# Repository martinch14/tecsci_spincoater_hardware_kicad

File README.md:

# tecsci_spincoater_hardware_kicad

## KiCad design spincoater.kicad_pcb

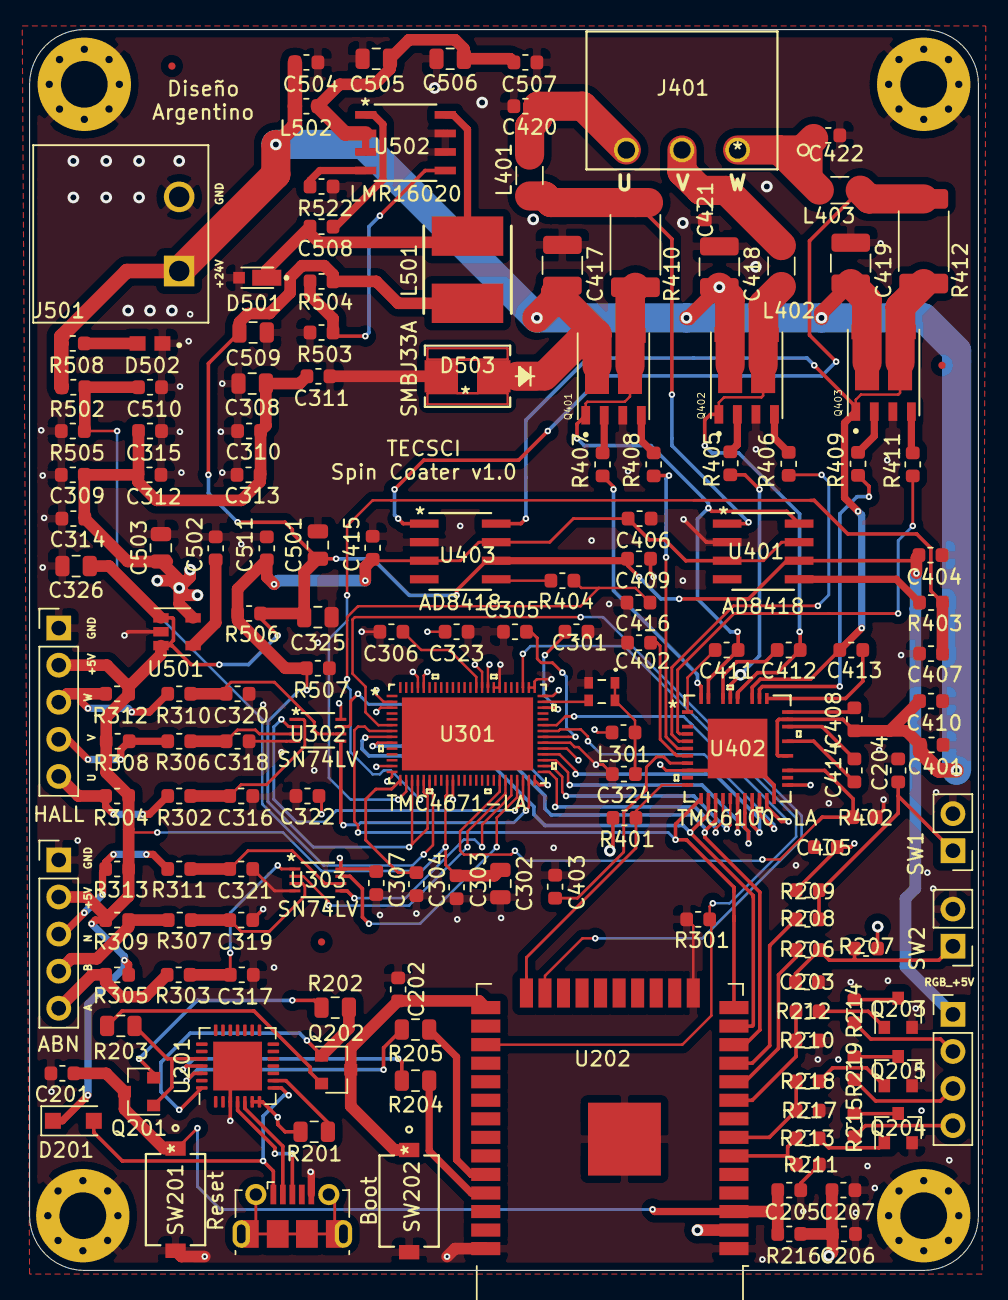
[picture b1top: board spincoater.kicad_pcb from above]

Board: 4 copper layers, 65.0 x 85.0 mm, 164 parts (0 on the bottom side), 112 nets.

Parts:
C201, C202, C205, C207: 0.1uF/50V/0603; C_0603_1608Metric
C203, C204, C301, C303, C304, C305, C306, C307, C310, C311, C312, C313, C314, C315, C322, C323, C404, C405, C406, C408, C409, C410, C415, C504, C507, C508, C510, C511: 100nF/50V/0603; C_0603_1608Metric
C206: 22uF/10V/0603; C_0603_1608Metric
C302, C308: 4.7uF/16V/0805; C_0805_2012Metric
C309, C411, C412, C413: 470nF/50V/0603; C_0603_1608Metric
C316, C317, C318, C319, C320, C321, C420, C421, C422: 1nF/100V/0603; C_0603_1608Metric
C324: 100nF/50V 0603; C_0603_1608Metric
C325, C326: 1uF/50V/0805; C_0805_2012Metric
C401: 100nF/50v/0603; C_0603_1608Metric
C402, C403: 2.2uF/16V/0603; C_0603_1608Metric
C407, C416: 2.2nF/50V/0603; C_0603_1608Metric
C414: 22nF/100V/0603; C_0603_1608Metric
C417, C418, C419: 10uF/50V/1210; C_1210_3225Metric
C501, C503, C509: 10uF/16V/0805; C_0805_2012Metric
C502: 10nF/16V/0603; C_0603_1608Metric
C505, C506: 2.2uF/50V/0805; C_0805_2012Metric
D201: PMEG3020EH; D_SOD-123F
D501: V2PM10HM3; DIODE_MSS1P4-M3
D502: LTST-C191TBKT-5A
D503: SMBJ33A; SMBJ33A-13-F
FID101, FID102, FID103: Fiducial; Fiducial_0.5mm_Mask1mm
H101, H102, H103, H104: MountingHole_Pad; MountingHole_3.2mm_M3_Pad_Via
J201: USB_B_Micro; USB_Micro-B_Molex-105017-0001
J202, J203: Conn_01x02; PinHeader_1x02_P2.54mm_Vertical
J204: Conn_01x04; PinHeader_1x04_P2.54mm_Vertical
J301, J302: Conn_01x05; PinHeader_1x05_P2.54mm_Vertical
J401: 1803280
J501: 1757242; PHOENIX_1757242
L301, L502: 600R/1A/0603; L_0603_1608Metric
L401, L402, L403: 50R/12A/1206; L_1206_3216Metric
L501: 15uH/2.5A/VLS6045; INDPM6060X450N
Q201, Q202: S8050; SOT-23
Q203, Q204, Q205: 2N7002; SOT-23
Q401, Q402, Q403: SI7288DP-T1-GE3; TRANS_SI7288DP-T1-GE3
R201: 4.7K/1%/0805; R_0805_2012Metric
R202, R203: 10K/1%/0805; R_0805_2012Metric
R204, R205: 1K/1%/0805; R_0805_2012Metric
R206, R208, R403, R506, R507: 1K/1%/0603; R_0603_1608Metric
R207, R209, R212, R213, R216, R218, R301, R401, R402, R505, R508: 10K/1%/0603; R_0603_1608Metric
R210, R211, R217: 330K/1%/0603; R_0603_1608Metric
R214, R215, R219: 680/1%/0603; R_0603_1608Metric
R302, R303, R304, R305, R306, R307, R308, R309, R310, R311, R312, R313: 4K7/1%/0603; R_0603_1608Metric
R404: 1k/1%/0603; R_0603_1608Metric
R405, R406, R407, R408, R409, R411: 10R/1%/0603; R_0603_1608Metric
R410, R412: 0R005/1%/3W/2512; R_2512_6332Metric
R502: 220K/1%/0603; R_0603_1608Metric
R503: 47K/1%/0603; R_0603_1608Metric
R504: 270K/1%/0603; R_0603_1608Metric
R522: 33K/1%/0603; R_0603_1608Metric
SW201: Reset; KSR223GLFG
SW202: Boot; KSR223GLFG
U201: CP2102N-A01-GQFN28; QFN-28-1EP_5x5mm_P0.5mm_EP3.35x3.35mm
U202: ESP32-WROOM-32D; ESP32-WROOM-32
U301: TMC4671-LA
U302, U303: SN74LV; SN74LVC3G17DCURE4
U401, U403: AD8418; AD8418WBRZ-RL
U402: TMC6100-LA
U501: LP2985-3.3; SOT-23-5
U502: LMR16020; LMR16020PDDAR
Y301: MC2016K25.0000C16ESH; MC2016K250000C16ESH

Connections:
+2.5V_REF: C406.1, C415.1, C511.1, R506.2, R507.1, U301.17, U301.19, U401.3, U401.7, U403.3, U403.7
+3V3: C206.1, C207.1, C307.1, C308.1, C309.1, C310.1, C311.1, C312.1, C313.1, C314.1, C315.1, C322.1, C323.2, C405.1, C503.1, L301.1, R201.1, R207.2, R209.2, R216.2, R401.1, U201.6, U201.7, U202.2, U301.2, U301.13, U301.43, U301.52, U301.61, U301.72, U302.8, U303.8, U402.16, U402.22, U501.5
+5V: C302.1, C303.1, C325.1, C326.1, C404.1, C409.1, C501.1, C509.1, D201.1, J204.1, J301.2, J302.2, L501.2, R304.2, R305.1, R308.1, R309.1, R312.2, R313.1, R504.1, R506.1, U301.23, U401.6, U403.6, U501.1, U501.3
+24V: C401.1, C408.1, C410.1, C417.1, C418.1, C419.1, C504.1, D503.1, J501.1, L502.1, Q401.7, Q401.8, Q401.9, Q402.7, Q402.8, Q402.9, Q403.7, Q403.8, Q403.9, R502.1, R508.1, U402.25, U402.28
/driverMotor/HSU: R407.2, U402.37
/driverMotor/HSV: R405.2, U402.34
/driverMotor/HSW: R409.2, U402.31
/driverMotor/LSU: R408.2, U402.5
/driverMotor/LSV: R406.2, U402.4
/driverMotor/LSW: R411.2, U402.3
/driverMotor/U: L401.1, R410.1, U401.1
/driverMotor/U_SENSE: C411.1, Q401.1, Q401.5, Q401.6, Q401.10, R410.2, U401.8, U402.36
/driverMotor/V: C412.1, L402.1, Q402.1, Q402.5, Q402.6, Q402.10, U402.33
/driverMotor/W: L403.1, R412.1, U403.1
/driverMotor/W_SENSE: C413.1, Q403.1, Q403.5, Q403.6, Q403.10, R412.2, U402.32, U403.8
/microcontroladorEsp/D+: J201.3, U201.4
/microcontroladorEsp/D-: J201.2, U201.5
/microcontroladorEsp/DTR: Q202.1, R202.2, U201.28
/microcontroladorEsp/EN: C201.1, C205.1, Q201.3, R216.1, SW201.1, U202.3
/microcontroladorEsp/IO0: C202.1, Q202.3, SW202.1, U202.25
/microcontroladorEsp/LED1: R210.1, R212.1, U202.9
/microcontroladorEsp/LED2: R211.1, R213.1, U202.6
/microcontroladorEsp/LED3: R217.1, R218.1, U202.7
/microcontroladorEsp/RTS: Q201.1, R203.2, U201.24
/microcontroladorEsp/RX: R205.1, U202.34
/microcontroladorEsp/SW1: R206.1, U202.10
/microcontroladorEsp/SW2: R208.1, U202.11
/microcontroladorEsp/TX: R204.1, U202.35
/microcontroladorEsp/VBUS: D201.2, J201.1, U201.8
ADC_+24: C510.1, R502.2, R505.1, U301.20
CS_4671: U202.23, U301.6
CS_6100: R401.2, U202.24, U402.10
CUR_U: C407.1, R403.1, U301.16
CUR_W: C416.1, R404.1, U301.18
EN_4671: R301.1, U202.27, U301.55
EN_6100: R402.2, U301.32, U402.24
GND: C201.2, C202.2, C203.2, C204.2, C205.2, C206.2, C207.2, C301.2, C302.2, C303.2, C304.2, C305.2, C306.2, C307.2, C308.2, C309.2, C310.2, C311.2, C312.2, C313.2, C314.2, C315.2, C316.2, C317.2, C318.2, C319.2, C320.2, C321.2, C322.2, C323.1, C324.2, C325.2, C326.2, C401.2, C402.2, C403.2, C404.2, C405.2, C406.2, C407.2, C409.2, C410.2, C415.2, C416.2, C417.2, C418.2, C419.2, C420.2, C421.2, C422.2, C501.2, C502.2, C503.2, C504.2, C505.2, C506.2, C507.2, C509.2, C510.2, C511.2, D501.2, D502.1, D503.2, H101.1, H102.1, H103.1, H104.1, J201.5, J202.2, J203.2, J301.1, J302.1, J501.2, Q203.2, Q204.2, Q205.2, Q401.3, Q402.3, Q403.3, R210.2, R211.2, R217.2, R301.2, R402.1, R503.2, R505.2, R507.2, R522.2, SW201.2, SW202.2, U201.3, U201.29, U202.1, U202.15, U202.38, U202.39, U301.3, U301.14, U301.24, U301.44, U301.53, U301.54, U301.59, U301.60, U301.62, U301.73, U302.4, U303.4, U401.2, U402.8, U402.21, U402.38, U403.2, U501.2, U502.6, U502.7, Y301.2
unnamed: C203.1, J202.1, R206.2, R207.1
unnamed: C204.1, J203.1, R208.2, R209.1
unnamed: C301.1, U301.50
unnamed: C304.1, U301.15
unnamed: C305.1, U301.45
unnamed: C306.1, U301.63
unnamed: C316.1, R302.2, U302.1
unnamed: C317.1, R303.1, U303.1
unnamed: C318.1, R306.1, U302.3
unnamed: C319.1, R307.1, U303.3
unnamed: C320.1, R310.2, U302.6
unnamed: C321.1, R311.1, U303.6
unnamed: C324.1, L301.2, Y301.1, Y301.4
unnamed: C402.1, U402.6
unnamed: C403.1, U402.7
unnamed: C408.2, U402.29
unnamed: C411.2, U402.1
unnamed: C412.2, U402.35
unnamed: C413.2, U402.30
unnamed: C414.1, U402.26
unnamed: C414.2, U402.27
unnamed: C420.1, J401.3, L401.2
unnamed: C421.1, J401.2, L402.2
unnamed: C422.1, J401.1, L403.2
unnamed: C502.1, U501.4
unnamed: C505.1, C506.1, C507.1, L502.2, U502.2, U502.3
unnamed: C508.1, D501.1, L501.1, U502.8
unnamed: C508.2, U502.1
unnamed: D502.2, R508.2
unnamed: J204.2, R214.1
unnamed: J204.3, R219.1
unnamed: J204.4, R215.1
unnamed: J301.3, R310.1, R312.1
unnamed: J301.4, R306.2, R308.2
unnamed: J301.5, R302.1, R304.1
unnamed: J302.3, R311.2, R313.2
unnamed: J302.4, R307.2, R309.2
unnamed: J302.5, R303.2, R305.2
unnamed: Q201.2, R202.1
unnamed: Q202.2, R203.1
unnamed: Q203.1, R212.2
unnamed: Q203.3, R214.2
unnamed: Q204.1, R213.2
unnamed: Q204.3, R215.2
unnamed: Q205.1, R218.2
unnamed: Q205.3, R219.2
unnamed: Q401.2, R407.1
unnamed: Q401.4, R408.1
unnamed: Q402.2, R405.1
unnamed: Q402.4, R406.1
unnamed: Q403.2, R409.1
unnamed: Q403.4, R411.1
unnamed: R201.2, U201.9
unnamed: R204.2, U201.25
unnamed: R205.2, U201.26
unnamed: R403.2, U401.5
unnamed: R404.2, U403.5
unnamed: R503.1, R504.2, U502.5
unnamed: R522.1, U502.4
unnamed: U301.33, U303.2
unnamed: U301.34, U303.5
unnamed: U301.35, U303.7
unnamed: U301.36, U302.2
unnamed: U301.37, U302.5
unnamed: U301.38, U302.7
unnamed: U301.51, Y301.3
SPI_MISO: U202.12, U301.9, U402.13
SPI_MOSI: U202.13, U301.8, U402.12
SPI_SCK: U202.14, U301.7, U402.11
UH: U301.39, U402.14
UL: U301.40, U402.15
VH: U301.41, U402.17
VL: U301.42, U402.18
WH: U301.46, U402.19
WL: U301.47, U402.20

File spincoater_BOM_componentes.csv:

"Id";"Designator";"Package";"Quantity";"Designation";"Supplier and ref";
1;"J204";"PinHeader_1x04_P2.54mm_Vertical";1;"Conn_01x04";;;
2;"R219,R215,R214";"R_0603_1608Metric";3;"680/1%/0603";;;
3;"R218,R508,R505,R402,R401,R301,R216,R213,R212,R209,R207";"R_0603_1608Metric";11;"10K/1%/0603";;;
4;"R217,R211,R210";"R_0603_1608Metric";3;"330K/1%/0603";;;
5;"Q205,Q204,Q203";"SOT-23";3;"2N7002";;;
6;"C504,C306,C511,C510,C508,C507,C415,C410,C409,C408,C406,C405,C404,C323,C322,C315,C314,C313,C312,C311,C310,C307,C305,C304,C303,C301,C204,C203";"C_0603_1608Metric";28;"100nF/50V/0603";;;
7;"U202";"ESP32-WROOM-32";1;"ESP32-WROOM-32D";;;
8;"D503";"SMBJ33A-13-F";1;"SMBJ33A";;;
9;"Q202,Q201";"SOT-23";2;"S8050";;;
10;"Y301";"MC2016K250000C16ESH";1;"MC2016K25.0000C16ESH";;;
11;"U502";"LMR16020PDDAR";1;"LMR16020";;;
12;"U501";"SOT-23-5";1;"LP2985-3.3";;;
13;"U403,U401";"AD8418WBRZ-RL";2;"AD8418";;;
14;"U402";"TMC6100-LA";1;"TMC6100-LA";;;
15;"U303,U302";"SN74LVC3G17DCURE4";2;"SN74LV";;;
16;"U301";"TMC4671-LA";1;"TMC4671-LA";;;
17;"U201";"QFN-28-1EP_5x5mm_P0.5mm_EP3.35x3.35mm";1;"CP2102N-A01-GQFN28";;;
18;"SW202";"KSR223GLFG";1;"Boot";;;
19;"SW201";"KSR223GLFG";1;"Reset";;;
20;"R522";"R_0603_1608Metric";1;"33K/1%/0603";;;
21;"R507,R506,R403,R208,R206";"R_0603_1608Metric";5;"1K/1%/0603";;;
22;"R504";"R_0603_1608Metric";1;"270K/1%/0603";;;
23;"R503";"R_0603_1608Metric";1;"47K/1%/0603";;;
24;"R502";"R_0603_1608Metric";1;"220K/1%/0603";;;
25;"R412,R410";"R_2512_6332Metric";2;"0R005/1%/3W/2512";;;
26;"R411,R409,R408,R407,R406,R405";"R_0603_1608Metric";6;"10R/1%/0603";;;
27;"R404";"R_0603_1608Metric";1;"1k/1%/0603";;;
28;"R313,R312,R311,R310,R309,R308,R307,R306,R305,R304,R303,R302";"R_0603_1608Metric";12;"4K7/1%/0603";;;
29;"R205,R204";"R_0805_2012Metric";2;"1K/1%/0805";;;
30;"R203,R202";"R_0805_2012Metric";2;"10K/1%/0805";;;
31;"R201";"R_0805_2012Metric";1;"4.7K/1%/0805";;;
32;"Q403,Q402,Q401";"TRANS_SI7288DP-T1-GE3";3;"SI7288DP-T1-GE3";;;
33;"L502,L301";"L_0603_1608Metric";2;"600R/1A/0603";;;
34;"L501";"INDPM6060X450N";1;"15uH/2.5A/VLS6045";;;
35;"L403,L402,L401";"L_1206_3216Metric";3;"50R/12A/1206";;;
36;"J501";"PHOENIX_1757242";1;"1757242";;;
37;"J401";"1803280";1;"1803280";;;
38;"J302,J301";"PinHeader_1x05_P2.54mm_Vertical";2;"Conn_01x05";;;
39;"J203,J202";"PinHeader_1x02_P2.54mm_Vertical";2;"Conn_01x02";;;
40;"J201";"USB_Micro-B_Molex-105017-0001";1;"USB_B_Micro";;;
41;"H104,H103,H102,H101";"MountingHole_3.2mm_M3_Pad_Via";4;"MountingHole_Pad";;;
42;"FID103,FID102,FID101";"Fiducial_0.5mm_Mask1mm";3;"Fiducial";;;
43;"D502";"LTST-C191TBKT-5A";1;"LTST-C191TBKT-5A";;;
44;"D501";"DIODE_MSS1P4-M3";1;"V2PM10HM3";;;
45;"D201";"D_SOD-123F";1;"PMEG3020EH";;;
46;"C509,C503,C501";"C_0805_2012Metric";3;"10uF/16V/0805";;;
47;"C506,C505";"C_0805_2012Metric";2;"2.2uF/50V/0805";;;
48;"C502";"C_0603_1608Metric";1;"10nF/16V/0603";;;
49;"C422,C421,C420,C321,C320,C319,C318,C317,C316";"C_0603_1608Metric";9;"1nF/100V/0603";;;
50;"C419,C418,C417";"C_1210_3225Metric";3;"10uF/50V/1210";;;
51;"C416,C407";"C_0603_1608Metric";2;"2.2nF/50V/0603";;;
52;"C414";"C_0603_1608Metric";1;"22nF/100V/0603";;;
53;"C413,C412,C411,C309";"C_0603_1608Metric";4;"470nF/50V/0603";;;
54;"C403,C402";"C_0603_1608Metric";2;"2.2uF/16V/0603";;;
55;"C401";"C_0603_1608Metric";1;"100nF/50v/0603";;;
56;"C326,C325";"C_0805_2012Metric";2;"1uF/50V/0805";;;
57;"C324";"C_0603_1608Metric";1;"100nF/50V 0603";;;
58;"C308,C302";"C_0805_2012Metric";2;"4.7uF/16V/0805";;;
59;"C207,C205,C202,C201";"C_0603_1608Metric";4;"0.1uF/50V/0603";;;
60;"C206";"C_0603_1608Metric";1;"22uF/10V/0603";;;

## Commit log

2020-06-23 primer commit
2020-07-11 ultima actualizacion antes de iniciar el ruteado, diseño verificado
2020-07-12 antes de comenzar a rutear
2020-07-14 ruteado terminado revision basica- 13_07_20
2020-07-17 enviado a fabricar
2020-12-16 agrego pdf con esquematico enviado a fabricar

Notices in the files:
parts and their libraries:
Copyright 2016 Accelerated Designs. All rights reserved.
